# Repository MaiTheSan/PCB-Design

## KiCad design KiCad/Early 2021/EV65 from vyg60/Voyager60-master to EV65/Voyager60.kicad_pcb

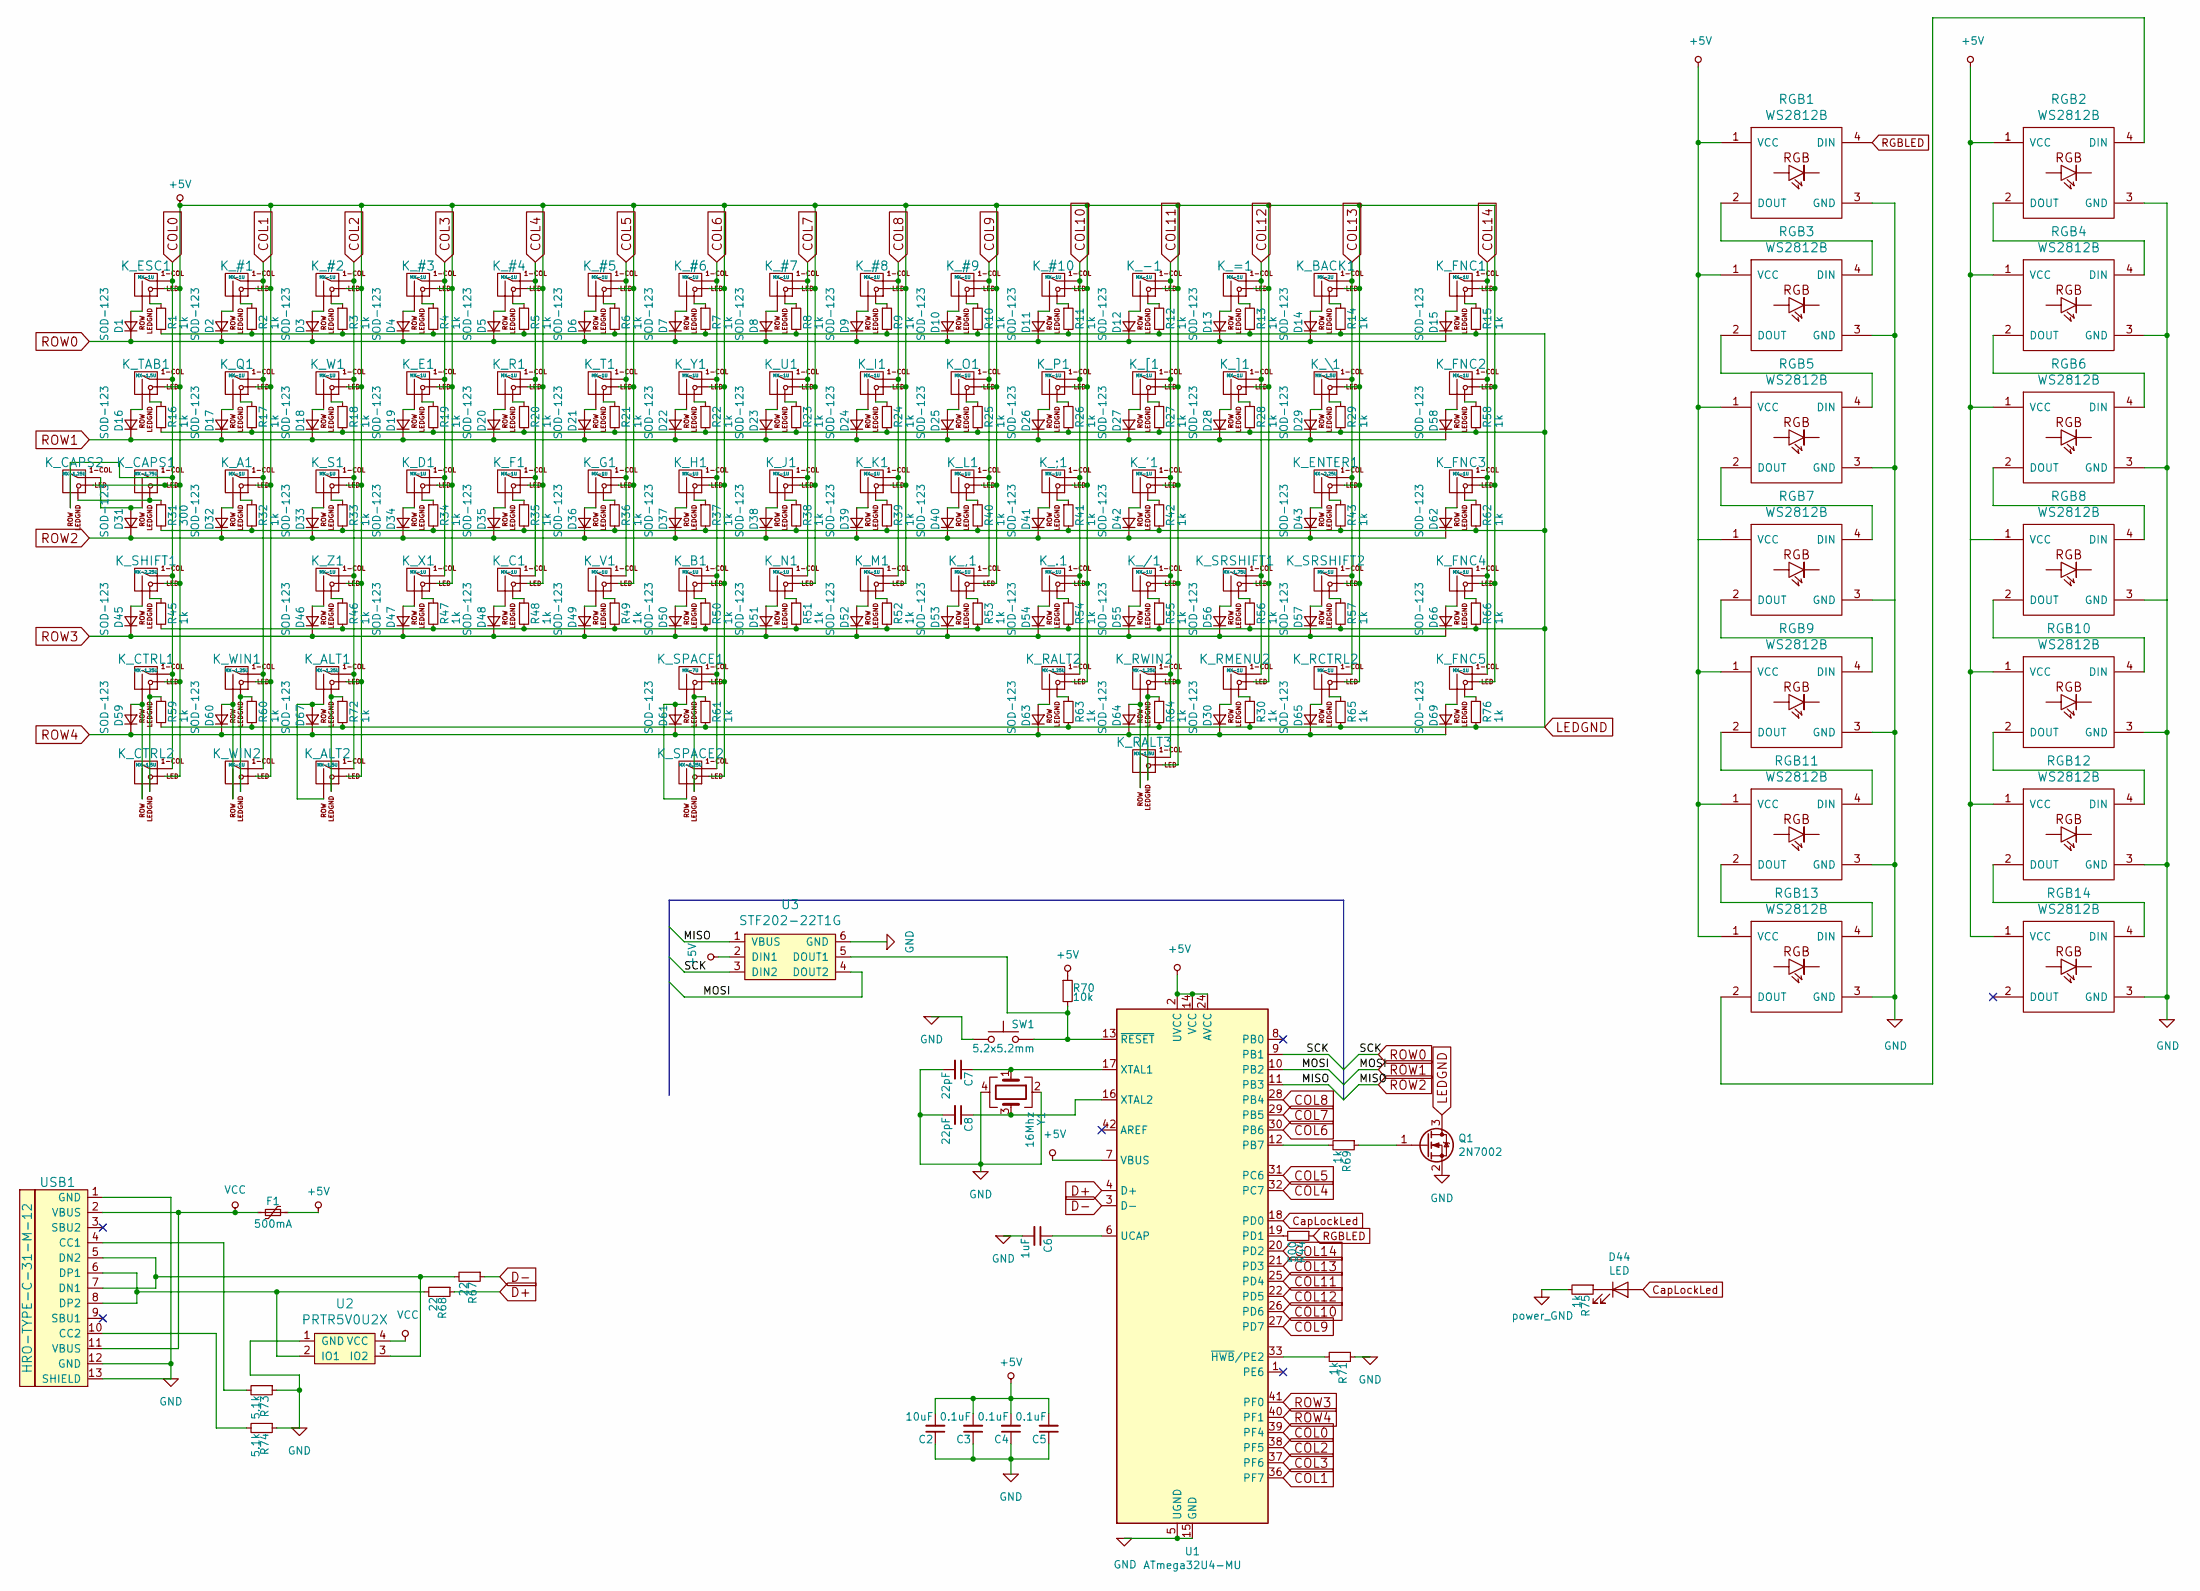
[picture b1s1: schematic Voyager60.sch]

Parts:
C2: 10uF; C_0603
C3, C4, C5: 0.1uF; C_0603
C6: 1uF; C_0603
C7, C8: 22pF; C_0603
D1, D2, D3, D4, D5, D6, D7, D8, D9, D10, D11, D12, D13, D14, D15, D16, D17, D18, D19, D20, D21, D22, D23, D24, D25, D26, D27, D28, D29, D30, D31, D32, D33, D34, D35, D36, D37, D38, D39, D40, D41, D42, D43, D45, D46, D47, D48, D49, D50, D51, D52, D53, D54, D55, D56, D57, D58, D59, D60, D61, D62, D63, D64, D65, D66, D67, D69: SOD-123; D_SOD-123
D44: LED; LED_D3.0mm
F1: 500mA; Fuse_SMD1206_Reflow
K_#1, K_#2, K_#3, K_#4, K_#5, K_#6, K_#7, K_#8, K_#9, K_#10: MX-1U; MXOnly-1U
K_'1: MX-1U; MXOnly-1U
K_,1: MX-1U; MXOnly-1U
K_-1: MX-1U; MXOnly-1U
K_.1: MX-1U; MXOnly-1U
K_/1: MX-1U; MXOnly-1U
K_;1: MX-1U; MXOnly-1U
K_=1: MX-1U; MXOnly-1U
K_A1: MX-1U; MXOnly-1U
K_ALT1: MX-1.25U; MXOnly-1.25U
K_ALT2: MX-1.5U; MXOnly-1.5U-FLIPPED
K_B1: MX-1U; MXOnly-1U
K_BACK1: MX-2U; MXOnly-2U
K_C1: MX-1U; MXOnly-1U
K_CAPS1: MX-1.75U; MXOnly-1.75U
K_CAPS2: MX-1.25U; MXOnly-1.25U-FLIPPED
K_CTRL1: MX-1.25U; MXOnly-1.25U
K_CTRL2: MX-1.5U; MXOnly-1.5U-FLIPPED
K_D1: MX-1U; MXOnly-1U
K_E1: MX-1U; MXOnly-1U
K_ENTER1: MX-2.25U; MXOnly-2.25U
K_ESC1: MX-1U; MXOnly-1U
K_F1: MX-1U; MXOnly-1U
K_FNC1, K_FNC2, K_FNC3, K_FNC4, K_FNC5: MX-1U; MXOnly-1U-FLIPPED
K_G1: MX-1U; MXOnly-1U
K_H1: MX-1U; MXOnly-1U
K_I1: MX-1U; MXOnly-1U
K_J1: MX-1U; MXOnly-1U
K_K1: MX-1U; MXOnly-1U
K_L1: MX-1U; MXOnly-1U
K_M1: MX-1U; MXOnly-1U
K_N1: MX-1U; MXOnly-1U
K_O1: MX-1U; MXOnly-1U
K_P1: MX-1U; MXOnly-1U
K_Q1: MX-1U; MXOnly-1U
K_R1: MX-1U; MXOnly-1U
K_RALT2: MX-1.25U; MXOnly-1.25U-FLIPPED
K_RALT3: MX-1.5U; MXOnly-1.5U-FLIPPED
K_RCTRL2: MX-1U; MXOnly-1U
K_RMENU2: MX-1U; MXOnly-1U
K_RWIN2: MX-1.25U; MXOnly-1.25U
K_S1: MX-1U; MXOnly-1U
K_SHIFT1: MX-2.25U; MXOnly-2.25U
K_SPACE1: MX-7U; MXOnly-7U-ReversedStabilizers
K_SPACE2: MX-6.25U; MXOnly-6.25U-ReversedStabilizers
K_SRSHIFT1: MX-1.75U; MXOnly-1.75U
K_SRSHIFT2: MX-1U; MXOnly-1U
K_T1: MX-1U; MXOnly-1U
K_TAB1: MX-1.5U; MXOnly-1.5U
K_U1: MX-1U; MXOnly-1U
K_V1: MX-1U; MXOnly-1U
K_W1: MX-1U; MXOnly-1U
K_WIN1: MX-1.25U; MXOnly-1.25U
K_WIN2: MX-1U; MXOnly-1U-FLIPPED
K_X1: MX-1U; MXOnly-1U
K_Y1: MX-1U; MXOnly-1U
K_Z1: MX-1U; MXOnly-1U
K_[1: MX-1U; MXOnly-1U
K_\1: MX-1.5U; MXOnly-1.5U
K_]1: MX-1U; MXOnly-1U
Q1: 2N7002; SOT-23
R1, R2, R3, R4, R5, R6, R7, R8, R9, R10, R11, R12, R13, R14, R15, R16, R17, R18, R19, R20, R21, R22, R23, R24, R25, R26, R27, R28, R29, R30, R32, R33, R34, R35, R36, R37, R38, R39, R40, R41, R42, R43, R45, R46, R47, R48, R49, R50, R51, R52, R53, R54, R55, R56, R57, R58, R59, R60, R61, R62, R63, R64, R65, R66, R69, R71, R72, R75, R76: 1k; R_0805
R31: 300; R_0805
R44: 500; R_0805
R67, R68: 22; R_0805
R70: 10k; R_0805
R73, R74: 5.1k; R_0805
RGB1, RGB2, RGB3, RGB4, RGB5, RGB6, RGB7, RGB8, RGB9, RGB10, RGB11, RGB12, RGB13, RGB14: WS2812B
SW1: 5.2x5.2mm; SKQG-1155865
U1: ATmega32U4-MU; QFN-44-1EP_7x7mm_Pitch0.5mm
U2: PRTR5V0U2X; SOT143B
U3: STF202-22T1G; Reset_Pretty
USB1: HRO-TYPE-C-31-M-12; HRO-TYPE-C-31-M-12-Assembly
Y1: 16Mhz; Crystal_SMD_3225-4Pin_3.2x2.5mm

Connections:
+5V: C2.2, C3.2, C4.2, C5.2, F1.1, K_#1.3 (LED), K_#2.3 (LED), K_#3.3 (LED), K_#4.3 (LED), K_#5.3 (LED), K_#6.3 (LED), K_#7.3 (LED), K_#8.3 (LED), K_#9.3 (LED), K_#10.3 (LED), K_'1.3 (LED), K_,1.3 (LED), K_-1.3 (LED), K_.1.3 (LED), K_/1.3 (LED), K_;1.3 (LED), K_=1.3 (LED), K_A1.3 (LED), K_ALT1.3 (LED), K_ALT2.3 (LED), K_B1.3 (LED), K_BACK1.3 (LED), K_C1.3 (LED), K_CAPS1.3 (LED), K_CAPS2.3 (LED), K_CTRL1.3 (LED), K_CTRL2.3 (LED), K_D1.3 (LED), K_E1.3 (LED), K_ENTER1.3 (LED), K_ESC1.3 (LED), K_F1.3 (LED), K_FNC1.3 (LED), K_FNC2.3 (LED), K_FNC3.3 (LED), K_FNC4.3 (LED), K_FNC5.3 (LED), K_G1.3 (LED), K_H1.3 (LED), K_I1.3 (LED), K_J1.3 (LED), K_K1.3 (LED), K_L1.3 (LED), K_M1.3 (LED), K_N1.3 (LED), K_O1.3 (LED), K_P1.3 (LED), K_Q1.3 (LED), K_R1.3 (LED), K_RALT2.3 (LED), K_RALT3.3 (LED), K_RCTRL2.3 (LED), K_RMENU2.3 (LED), K_RWIN2.3 (LED), K_S1.3 (LED), K_SHIFT1.3 (LED), K_SPACE1.3 (LED), K_SPACE2.3 (LED), K_SRSHIFT1.3 (LED), K_SRSHIFT2.3 (LED), K_T1.3 (LED), K_TAB1.3 (LED), K_U1.3 (LED), K_V1.3 (LED), K_W1.3 (LED), K_WIN1.3 (LED), K_WIN2.3 (LED), K_X1.3 (LED), K_Y1.3 (LED), K_Z1.3 (LED), K_[1.3 (LED), K_\1.3 (LED), K_]1.3 (LED), R70.1, RGB1.1 (VCC), RGB2.1 (VCC), RGB3.1 (VCC), RGB4.1 (VCC), RGB5.1 (VCC), RGB6.1 (VCC), RGB7.1 (VCC), RGB8.1 (VCC), RGB9.1 (VCC), RGB10.1 (VCC), RGB11.1 (VCC), RGB12.1 (VCC), RGB13.1 (VCC), RGB14.1 (VCC), U1.2 (UVCC), U1.7 (VBUS), U1.14 (VCC), U1.24 (AVCC), U1.34 (VCC), U1.44 (AVCC), U3.2 (DIN1)
COL0: K_CAPS1.1 (COL), K_CAPS2.2 (ROW), K_CTRL1.1 (COL), K_CTRL2.1 (COL), K_ESC1.1 (COL), K_SHIFT1.1 (COL), K_TAB1.1 (COL), U1.39 (PF4)
COL1: K_#1.1 (COL), K_A1.1 (COL), K_Q1.1 (COL), K_WIN1.1 (COL), K_WIN2.1 (COL), U1.36 (PF7)
COL2: K_#2.1 (COL), K_ALT1.1 (COL), K_ALT2.1 (COL), K_S1.1 (COL), K_W1.1 (COL), K_Z1.1 (COL), U1.38 (PF5)
COL3: K_#3.1 (COL), K_D1.1 (COL), K_E1.1 (COL), K_X1.1 (COL), U1.37 (PF6)
COL4: K_#4.1 (COL), K_C1.1 (COL), K_F1.1 (COL), K_R1.1 (COL), U1.32 (PC7)
COL5: K_#5.1 (COL), K_G1.1 (COL), K_T1.1 (COL), K_V1.1 (COL), U1.31 (PC6)
COL6: K_#6.1 (COL), K_B1.1 (COL), K_H1.1 (COL), K_SPACE1.1 (COL), K_SPACE2.1 (COL), K_Y1.1 (COL), U1.30 (PB6)
COL7: K_#7.1 (COL), K_J1.1 (COL), K_N1.1 (COL), K_U1.1 (COL), U1.29 (PB5)
COL8: K_#8.1 (COL), K_I1.1 (COL), K_K1.1 (COL), K_M1.1 (COL), U1.28 (PB4)
COL9: K_#9.1 (COL), K_,1.1 (COL), K_L1.1 (COL), K_O1.1 (COL), U1.27 (PD7)
COL10: K_#10.1 (COL), K_.1.1 (COL), K_;1.1 (COL), K_P1.1 (COL), K_RALT2.1 (COL), U1.26 (PD6)
COL11: K_'1.1 (COL), K_-1.1 (COL), K_/1.1 (COL), K_RALT3.1 (COL), K_RWIN2.1 (COL), K_[1.1 (COL), U1.25 (PD4)
COL12: K_=1.1 (COL), K_RMENU2.1 (COL), K_SRSHIFT1.1 (COL), K_]1.1 (COL), U1.22 (PD5)
COL13: K_BACK1.1 (COL), K_ENTER1.1 (COL), K_RCTRL2.1 (COL), K_SRSHIFT2.1 (COL), K_\1.1 (COL), U1.21 (PD3)
COL14: K_FNC1.1 (COL), K_FNC2.1 (COL), K_FNC3.1 (COL), K_FNC4.1 (COL), K_FNC5.1 (COL), U1.20 (PD2)
CapLockLed: D44.2 (A), U1.18 (PD0)
D+: R68.1, U1.4 (D+)
D-: R67.1, U1.3 (D-)
LEDGND: Q1.3 (D), R1.2, R2.2, R3.2, R4.2, R5.2, R6.2, R7.2, R8.2, R9.2, R10.2, R11.2, R12.2, R13.2, R14.2, R15.2, R16.2, R17.2, R18.2, R19.2, R20.2, R21.2, R22.2, R23.2, R24.2, R25.2, R26.2, R27.2, R28.2, R29.2, R30.2, R31.2, R32.2, R33.2, R34.2, R35.2, R36.2, R37.2, R38.2, R39.2, R40.2, R41.2, R42.2, R43.2, R45.2, R46.2, R47.2, R48.2, R49.2, R50.2, R51.2, R52.2, R53.2, R54.2, R55.2, R56.2, R57.2, R58.2, R59.2, R60.2, R61.2, R62.2, R63.2, R64.2, R65.2, R66.2, R72.2, R76.2
unnamed: C6.1, U1.6 (UCAP)
unnamed: C7.1, U1.17 (XTAL1), Y1.1
unnamed: C8.1, U1.16 (XTAL2), Y1.3
unnamed: D1.2 (A), K_ESC1.2 (ROW)
unnamed: D2.2 (A), K_#1.2 (ROW)
unnamed: D3.2 (A), K_#2.2 (ROW)
unnamed: D4.2 (A), K_#3.2 (ROW)
unnamed: D5.2 (A), K_#4.2 (ROW)
unnamed: D6.2 (A), K_#5.2 (ROW)
unnamed: D7.2 (A), K_#6.2 (ROW)
unnamed: D8.2 (A), K_#7.2 (ROW)
unnamed: D9.2 (A), K_#8.2 (ROW)
unnamed: D10.2 (A), K_#9.2 (ROW)
unnamed: D11.2 (A), K_#10.2 (ROW)
unnamed: D12.2 (A), K_-1.2 (ROW)
unnamed: D13.2 (A), K_=1.2 (ROW)
unnamed: D14.2 (A), K_BACK1.2 (ROW)
unnamed: D15.2 (A), K_FNC1.2 (ROW)
unnamed: D16.2 (A), K_TAB1.2 (ROW)
unnamed: D17.2 (A), K_Q1.2 (ROW)
unnamed: D18.2 (A), K_W1.2 (ROW)
unnamed: D19.2 (A), K_E1.2 (ROW)
unnamed: D20.2 (A), K_R1.2 (ROW)
unnamed: D21.2 (A), K_T1.2 (ROW)
unnamed: D22.2 (A), K_Y1.2 (ROW)
unnamed: D23.2 (A), K_U1.2 (ROW)
unnamed: D24.2 (A), K_I1.2 (ROW)
unnamed: D25.2 (A), K_O1.2 (ROW)
unnamed: D26.2 (A), K_P1.2 (ROW)
unnamed: D27.2 (A), K_[1.2 (ROW)
unnamed: D28.2 (A), K_]1.2 (ROW)
unnamed: D29.2 (A), K_\1.2 (ROW)
unnamed: D30.2 (A), K_RMENU2.2 (ROW)
unnamed: D31.2 (A), K_CAPS1.2 (ROW), K_CAPS2.1 (COL)
unnamed: D32.2 (A), K_A1.2 (ROW)
unnamed: D33.2 (A), K_S1.2 (ROW)
unnamed: D34.2 (A), K_D1.2 (ROW)
unnamed: D35.2 (A), K_F1.2 (ROW)
unnamed: D36.2 (A), K_G1.2 (ROW)
unnamed: D37.2 (A), K_H1.2 (ROW)
unnamed: D38.2 (A), K_J1.2 (ROW)
unnamed: D39.2 (A), K_K1.2 (ROW)
unnamed: D40.2 (A), K_L1.2 (ROW)
unnamed: D41.2 (A), K_;1.2 (ROW)
unnamed: D42.2 (A), K_'1.2 (ROW)
unnamed: D43.2 (A), K_ENTER1.2 (ROW)
unnamed: D44.1 (K), R75.1
unnamed: D45.2 (A), K_SHIFT1.2 (ROW)
unnamed: D46.2 (A), K_Z1.2 (ROW)
unnamed: D47.2 (A), K_X1.2 (ROW)
unnamed: D48.2 (A), K_C1.2 (ROW)
unnamed: D49.2 (A), K_V1.2 (ROW)
unnamed: D50.2 (A), K_B1.2 (ROW)
unnamed: D51.2 (A), K_N1.2 (ROW)
unnamed: D52.2 (A), K_M1.2 (ROW)
unnamed: D53.2 (A), K_,1.2 (ROW)
unnamed: D54.2 (A), K_.1.2 (ROW)
unnamed: D55.2 (A), K_/1.2 (ROW)
unnamed: D56.2 (A), K_SRSHIFT1.2 (ROW)
unnamed: D57.2 (A), K_SRSHIFT2.2 (ROW)
unnamed: D58.2 (A), K_FNC2.2 (ROW)
unnamed: D59.2 (A), K_CTRL1.2 (ROW), K_CTRL2.2 (ROW)
unnamed: D60.2 (A), K_WIN1.2 (ROW), K_WIN2.2 (ROW)
unnamed: D61.2 (A), K_SPACE1.2 (ROW), K_SPACE2.2 (ROW)
unnamed: D62.2 (A), K_FNC3.2 (ROW)
unnamed: D63.2 (A), K_RALT2.2 (ROW)
unnamed: D64.2 (A), K_RALT3.2 (ROW), K_RWIN2.2 (ROW)
unnamed: D65.2 (A), K_RCTRL2.2 (ROW)
unnamed: D66.2 (A), K_FNC4.2 (ROW)
unnamed: D67.2 (A), K_ALT1.2 (ROW), K_ALT2.2 (ROW)
unnamed: D69.2 (A), K_FNC5.2 (ROW)
unnamed: K_#1.4 (LEDGND), R2.1
unnamed: K_#2.4 (LEDGND), R3.1
unnamed: K_#3.4 (LEDGND), R4.1
unnamed: K_#4.4 (LEDGND), R5.1
unnamed: K_#5.4 (LEDGND), R6.1
unnamed: K_#6.4 (LEDGND), R7.1
unnamed: K_#7.4 (LEDGND), R8.1
unnamed: K_#8.4 (LEDGND), R9.1
unnamed: K_#9.4 (LEDGND), R10.1
unnamed: K_#10.4 (LEDGND), R11.1
unnamed: K_'1.4 (LEDGND), R42.1
unnamed: K_,1.4 (LEDGND), R53.1
unnamed: K_-1.4 (LEDGND), R12.1
unnamed: K_.1.4 (LEDGND), R54.1
unnamed: K_/1.4 (LEDGND), R55.1
unnamed: K_;1.4 (LEDGND), R41.1
unnamed: K_=1.4 (LEDGND), R13.1
unnamed: K_A1.4 (LEDGND), R32.1
unnamed: K_ALT1.4 (LEDGND), K_ALT2.4 (LEDGND), R72.1
unnamed: K_B1.4 (LEDGND), R50.1
unnamed: K_BACK1.4 (LEDGND), R14.1
unnamed: K_C1.4 (LEDGND), R48.1
unnamed: K_CAPS1.4 (LEDGND), K_CAPS2.4 (LEDGND), R31.1
unnamed: K_CTRL1.4 (LEDGND), K_CTRL2.4 (LEDGND), R59.1
unnamed: K_D1.4 (LEDGND), R34.1
unnamed: K_E1.4 (LEDGND), R19.1
unnamed: K_ENTER1.4 (LEDGND), R43.1
unnamed: K_ESC1.4 (LEDGND), R1.1
unnamed: K_F1.4 (LEDGND), R35.1
unnamed: K_FNC1.4 (LEDGND), R15.1
unnamed: K_FNC2.4 (LEDGND), R58.1
unnamed: K_FNC3.4 (LEDGND), R62.1
unnamed: K_FNC4.4 (LEDGND), R66.1
unnamed: K_FNC5.4 (LEDGND), R76.1
unnamed: K_G1.4 (LEDGND), R36.1
unnamed: K_H1.4 (LEDGND), R37.1
unnamed: K_I1.4 (LEDGND), R24.1
unnamed: K_J1.4 (LEDGND), R38.1
unnamed: K_K1.4 (LEDGND), R39.1
unnamed: K_L1.4 (LEDGND), R40.1
unnamed: K_M1.4 (LEDGND), R52.1
unnamed: K_N1.4 (LEDGND), R51.1
unnamed: K_O1.4 (LEDGND), R25.1
unnamed: K_P1.4 (LEDGND), R26.1
unnamed: K_Q1.4 (LEDGND), R17.1
unnamed: K_R1.4 (LEDGND), R20.1
unnamed: K_RALT2.4 (LEDGND), R63.1
unnamed: K_RALT3.4 (LEDGND), K_RWIN2.4 (LEDGND), R64.1
unnamed: K_RCTRL2.4 (LEDGND), R65.1
unnamed: K_RMENU2.4 (LEDGND), R30.1
unnamed: K_S1.4 (LEDGND), R33.1
unnamed: K_SHIFT1.4 (LEDGND), R45.1
unnamed: K_SPACE1.4 (LEDGND), K_SPACE2.4 (LEDGND), R61.1
unnamed: K_SRSHIFT1.4 (LEDGND), R56.1
unnamed: K_SRSHIFT2.4 (LEDGND), R57.1
unnamed: K_T1.4 (LEDGND), R21.1
unnamed: K_TAB1.4 (LEDGND), R16.1
unnamed: K_U1.4 (LEDGND), R23.1
unnamed: K_V1.4 (LEDGND), R49.1
unnamed: K_W1.4 (LEDGND), R18.1
unnamed: K_WIN1.4 (LEDGND), K_WIN2.4 (LEDGND), R60.1
unnamed: K_X1.4 (LEDGND), R47.1
unnamed: K_Y1.4 (LEDGND), R22.1
unnamed: K_Z1.4 (LEDGND), R46.1
unnamed: K_[1.4 (LEDGND), R27.1
unnamed: K_\1.4 (LEDGND), R29.1
unnamed: K_]1.4 (LEDGND), R28.1
unnamed: Q1.1 (G), R69.1
unnamed: R44.2, U1.19 (PD1)
unnamed: R67.2, U2.3 (IO2), USB1.5 (DN2), USB1.7 (DN1)
unnamed: R68.2, U2.2 (IO1), USB1.6 (DP1), USB1.8 (DP2)
unnamed: R69.2, U1.12 (PB7)
unnamed: R70.2, SW1.2, U1.13 (~RESET), U3.5 (DOUT1)
unnamed: R71.2, U1.33 (~HWB~/PE2)
unnamed: R73.2, USB1.4 (CC1)
unnamed: R74.2, USB1.10 (CC2)
unnamed: RGB1.2 (DOUT), RGB3.4 (DIN)
unnamed: RGB2.2 (DOUT), RGB4.4 (DIN)
unnamed: RGB3.2 (DOUT), RGB5.4 (DIN)
unnamed: RGB4.2 (DOUT), RGB6.4 (DIN)
unnamed: RGB5.2 (DOUT), RGB7.4 (DIN)
unnamed: RGB6.2 (DOUT), RGB8.4 (DIN)
unnamed: RGB7.2 (DOUT), RGB9.4 (DIN)
unnamed: RGB10.2 (DOUT), RGB12.4 (DIN)
unnamed: RGB8.2 (DOUT), RGB10.4 (DIN)
unnamed: RGB11.2 (DOUT), RGB13.4 (DIN)
unnamed: RGB9.2 (DOUT), RGB11.4 (DIN)
unnamed: RGB12.2 (DOUT), RGB14.4 (DIN)
unnamed: RGB2.4 (DIN), RGB13.2 (DOUT)
RGBLED: R44.1, RGB1.4 (DIN)
ROW0: D1.1 (K), D2.1 (K), D3.1 (K), D4.1 (K), D5.1 (K), D6.1 (K), D7.1 (K), D8.1 (K), D9.1 (K), D10.1 (K), D11.1 (K), D12.1 (K), D13.1 (K), D14.1 (K), D15.1 (K), U1.9 (PB1), U3.3 (DIN2)
ROW1: D16.1 (K), D17.1 (K), D18.1 (K), D19.1 (K), D20.1 (K), D21.1 (K), D22.1 (K), D23.1 (K), D24.1 (K), D25.1 (K), D26.1 (K), D27.1 (K), D28.1 (K), D29.1 (K), D58.1 (K), U1.10 (PB2), U3.4 (DOUT2)
ROW2: D31.1 (K), D32.1 (K), D33.1 (K), D34.1 (K), D35.1 (K), D36.1 (K), D37.1 (K), D38.1 (K), D39.1 (K), D40.1 (K), D41.1 (K), D42.1 (K), D43.1 (K), D62.1 (K), U1.11 (PB3), U3.1 (VBUS)
ROW3: D45.1 (K), D46.1 (K), D47.1 (K), D48.1 (K), D49.1 (K), D50.1 (K), D51.1 (K), D52.1 (K), D53.1 (K), D54.1 (K), D55.1 (K), D56.1 (K), D57.1 (K), D66.1 (K), U1.41 (PF0)
ROW4: D30.1 (K), D59.1 (K), D60.1 (K), D61.1 (K), D63.1 (K), D64.1 (K), D65.1 (K), D67.1 (K), D69.1 (K), U1.40 (PF1)
VCC: F1.2, U2.4 (VCC), USB1.2 (VBUS), USB1.11 (VBUS)

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
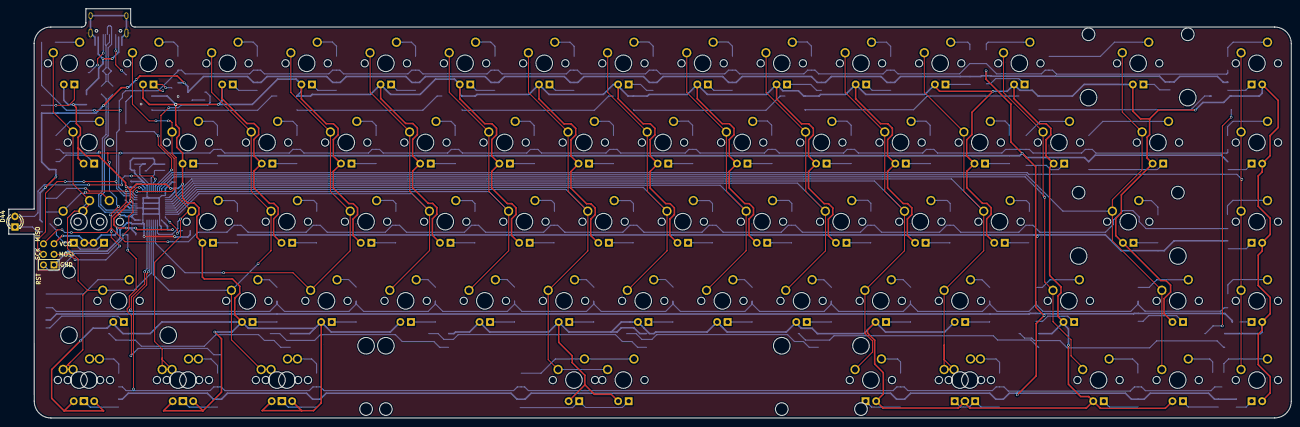
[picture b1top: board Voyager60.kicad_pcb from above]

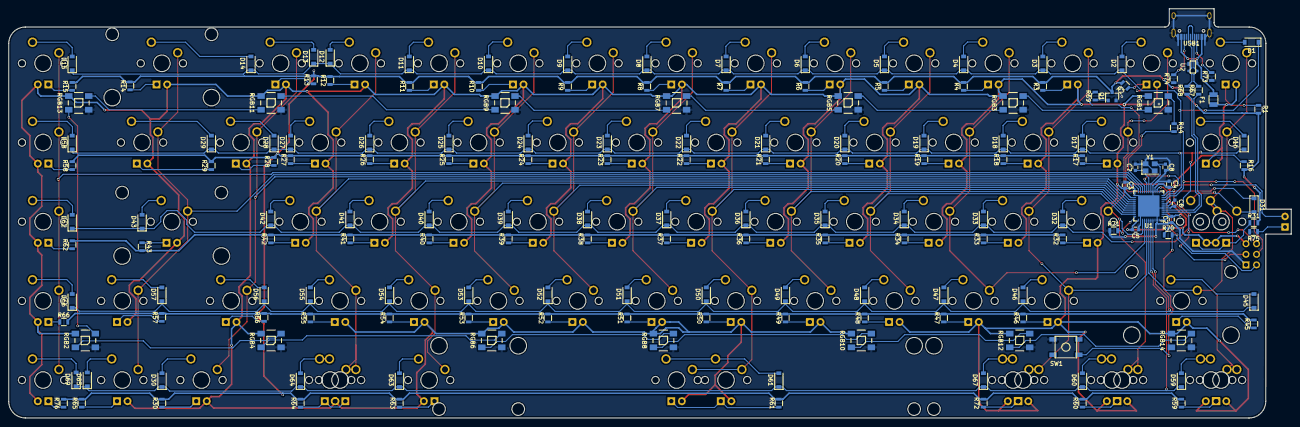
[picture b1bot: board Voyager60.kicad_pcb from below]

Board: 2 copper layers, 308.5 x 98.4 mm, 246 parts (171 on the bottom side), 188 nets.

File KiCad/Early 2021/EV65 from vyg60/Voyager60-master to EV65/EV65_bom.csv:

Component,Description,Part,References,Value,Footprint,Quantity Per PCB,Datasheet
1,"Capacitor, Ceramic, 15V or more",C_Small,C3 C4 C5,0.1uF,C_0603,3,
2,"Capacitor, Ceramic, 15V or more",C_Small,C2,10uF,C_0603,1,
3,"Capacitor, Ceramic, 15V or more",C_Small,C6,1uF,C_0603,1,
4,"Capacitor, Ceramic, 15V or more",C_Small,C7 C8,22pF,C_0603,2,
5,"Diode, Generic",D_Small,D1 D2 D3 D4 D5 D6 D7 D8 D9 D10 D11 D12 D13 D14 D16 D17 D18 D19 D20 D21 D22 D23 D24 D25 D26 D27 D28 D29 D30 D31 D32 D33 D34 D35 D36 D37 D38 D39 D40 D41 D42 D43 D45 D46 D47 D48 D49 D50 D51 D52 D53 D54 D55 D56 D57 D58 D59 D60 D61 D62 D63 D64 D65 D67 D69,SOD-123,D_SOD-123,66,
6,"Polyfuse, 500mA hold, 1A trip",Polyfuse_Small,F1,500mA,Fuse_SMD1206_Reflow,1,
7,N-Channel MOSFET,2N7002,Q1,2N7002,SOT-23,1,https://www.fairchildsemi.com/datasheets/2N/2N7002.pdf
8,"Resistor, Generic",R_Small,R70,10k,R_0805,1,
9,"resistor, Generic",R_Small,R31,300,R_0805,1,
10,"Resistor, Generic",R_Small,R1 R2 R3 R4 R5 R6 R7 R8 R9 R10 R11 R12 R13 R14 R16 R17 R18 R19 R20 R21 R22 R23 R24 R25 R26 R27 R28 R29 R30 R32 R33 R34 R35 R36 R37 R38 R39 R40 R41 R42 R43 R45 R46 R47 R48 R49 R50 R51 R52 R53 R54 R55 R56 R57 R58 R59 R60 R61 R62 R63 R64 R65 R66 R69 R71 R72 R76,1k,R_0805,69,
11,"Resistor, Generic",R_Small,R67 R68,22,R_0805,2,
12,"Resistor, Generic",R_Small,R73 R74,5.1k,R_0805,2,
13,"Resistor, Generic",R_Small,R44,500,R_0805,1,
14,"WS2812B RGB LED, 5050",WS2812B,RGB1 RGB2 RGB3 RGB4 RGB5 RGB6 RGB7 RGB8 RGB9 RGB10 RGB11 RGB12 RGB13 RGB14,WS2812B,WS2812B,14,
15,"5.2 x 5.2mm Push Button, SMT",SW_Push,SW1,5.2x5.2mm,SKQG-1155865,1,
16,ATmega32U4-MU,ATmega32U4-MU-MCU_Microchip_ATmega,U1,ATmega32U4-MU,QFN-44-1EP_7x7mm_Pitch0.5mm,1,http://ww1.microchip.com/downloads/en/DeviceDoc/Atmel-7766-8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
17,ESD Protection IC,PRTR5V0U2X,U2,PRTR5V0U2X,SOT143B,1,
18,USB Type-C Connector,HRO-TYPE-C-31-M-12,USB1,HRO-TYPE-C-31-M-12,HRO-TYPE-C-31-M-12-Assembly,1,
,"Crystal, 3.2 x 2.5mm, 16MHz",Crystal_GND24,Y1,16Mhz,Crystal_SMD_3225-4pin_3.2x2.5mm,1,

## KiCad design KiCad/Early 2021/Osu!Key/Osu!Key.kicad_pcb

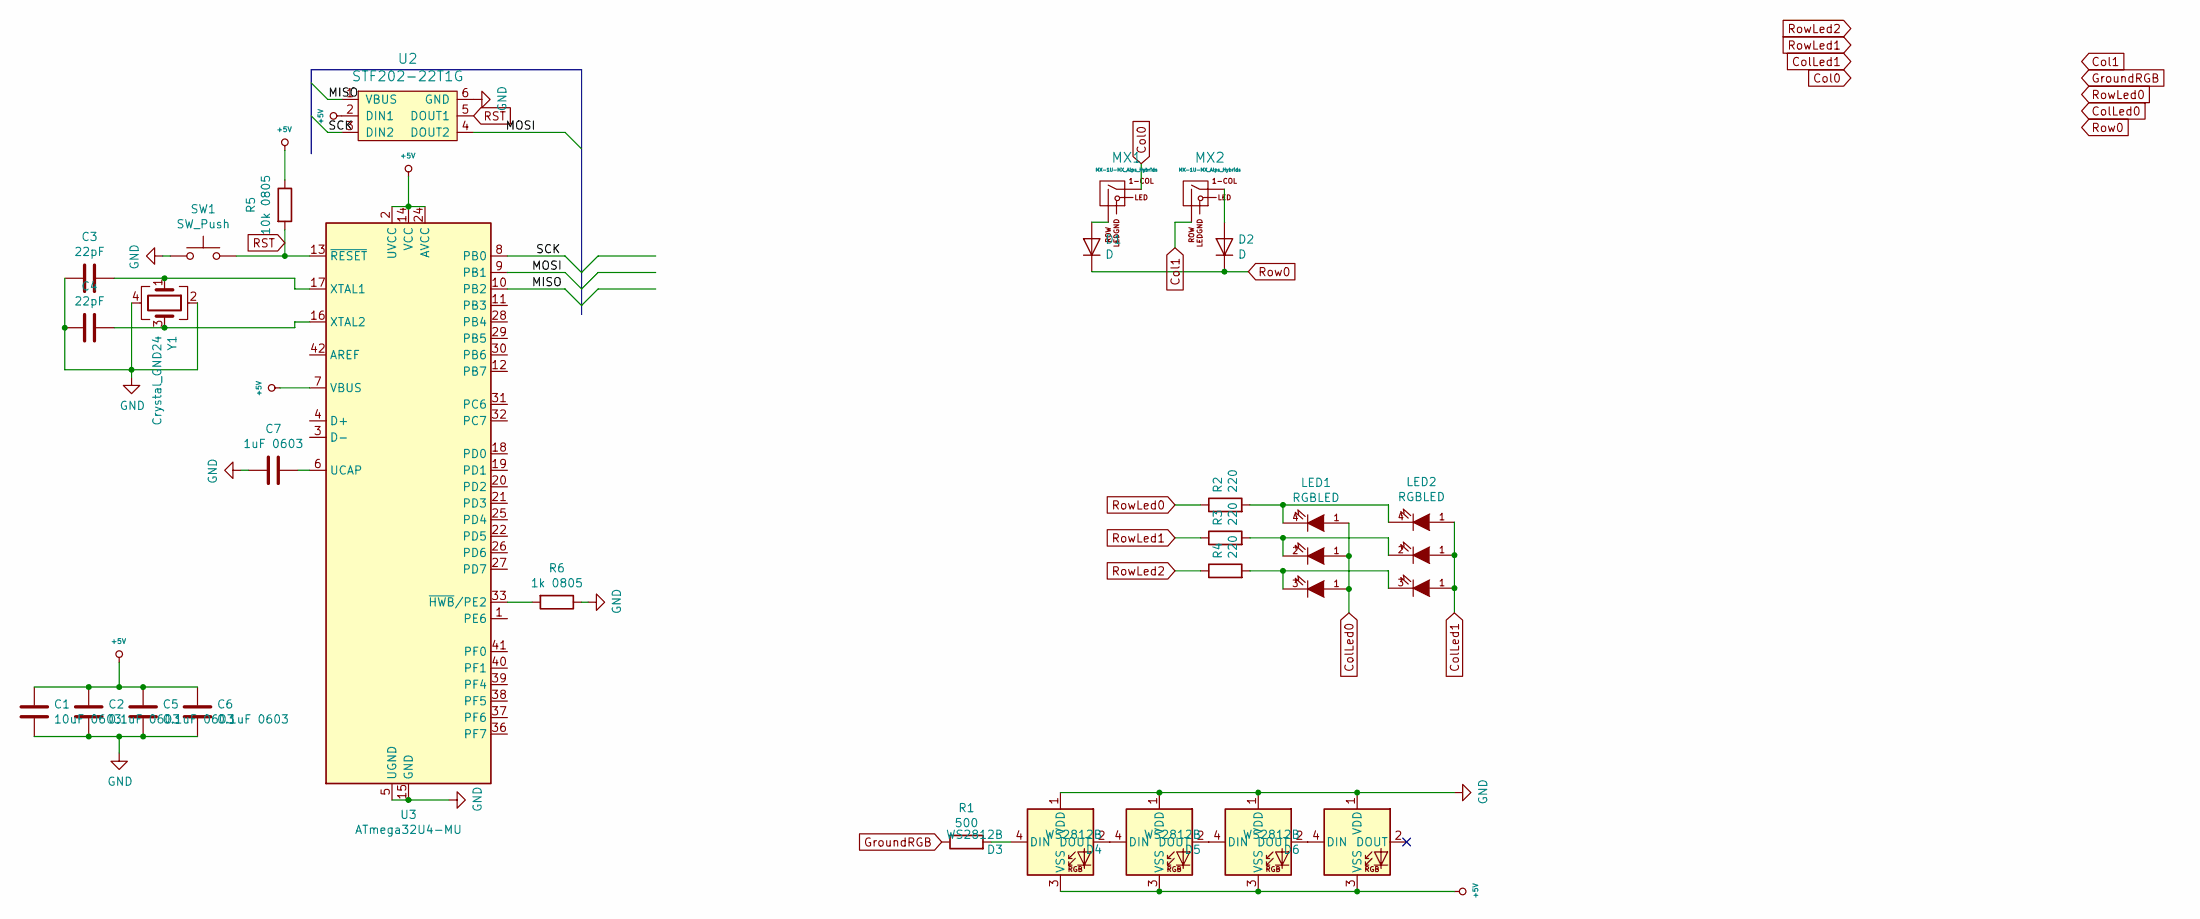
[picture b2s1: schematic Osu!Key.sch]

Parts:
C1: 10uF 0603; C_0603
C2, C5, C6: 0.1uF 0603; C_0603
C3, C4: 22pF; C_0603
C7: 1uF 0603; C_0603
D1, D2: D; D_SOD-123-Pretty
D3, D4, D5, D6: WS2812B; LED_WS2812B_PLCC4_5.0x5.0mm_P3.2mm
LED1, LED2: RGBLED; RGB-6028
MX1, MX2: MX-1U-MX_Alps_Hybrids; MXOnly-1U-Hotswap
R1: 500; R_0805
R2, R3, R4: 220; R_0805
R5: 10k 0805; R_0805
R6: 1k 0805; R_0805
SW1: SW_Push; SKQGADE010
U2: STF202-22T1G; Reset_Pretty
U3: ATmega32U4-MU; QFN-44-1EP_7x7mm_P0.5mm_EP5.2x5.2mm
Y1: Crystal_GND24; Crystal_SMD_3225-4Pin_3.2x2.5mm

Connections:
+5V: C1.1, C2.1, C5.1, C6.1, D3.3 (VSS), D4.3 (VSS), D5.3 (VSS), D6.3 (VSS), R5.1, U2.2 (DIN1), U3.2 (UVCC), U3.7 (VBUS), U3.14 (VCC), U3.24 (AVCC), U3.34 (VCC), U3.44 (AVCC)
/MISO: U2.1 (VBUS), U3.10 (PB2)
/MOSI: U2.4 (DOUT2), U3.9 (PB1)
/SCK: U2.3 (DIN2), U3.8 (PB0)
Col0: MX1.1 (COL)
ColLed0: LED1.1 (A)
ColLed1: LED2.1 (A)
GND: C1.2, C2.2, C3.2, C4.2, C5.2, C6.2, C7.2, D3.1 (VDD), D4.1 (VDD), D5.1 (VDD), D6.1 (VDD), R6.1, SW1.1, U2.6 (GND), U3.5 (UGND), U3.15 (GND), U3.23 (GND), U3.35 (GND), U3.43 (GND), U3.45 (GND), Y1.2, Y1.4
GroundRGB: R1.1
unnamed: C3.1, U3.17 (XTAL1), Y1.1
unnamed: C4.1, U3.16 (XTAL2), Y1.3
unnamed: C7.1, U3.6 (UCAP)
unnamed: D1.2 (A), MX1.2 (ROW)
unnamed: D3.2 (DOUT), D4.4 (DIN)
unnamed: D3.4 (DIN), R1.2
unnamed: D4.2 (DOUT), D5.4 (DIN)
unnamed: D5.2 (DOUT), D6.4 (DIN)
unnamed: LED1.2 (R), LED2.2 (R), R3.2
unnamed: LED1.3 (G), LED2.3 (G), R4.2
unnamed: LED1.4 (B), LED2.4 (B), R2.2
unnamed: R6.2, U3.33 (~HWB~/PE2)
RST: R5.2, SW1.2, U2.5 (DOUT1), U3.13 (~RESET)
Row0: D1.1 (K), D2.1 (K)
RowLed0: R2.1
RowLed1: R3.1
RowLed2: R4.1

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
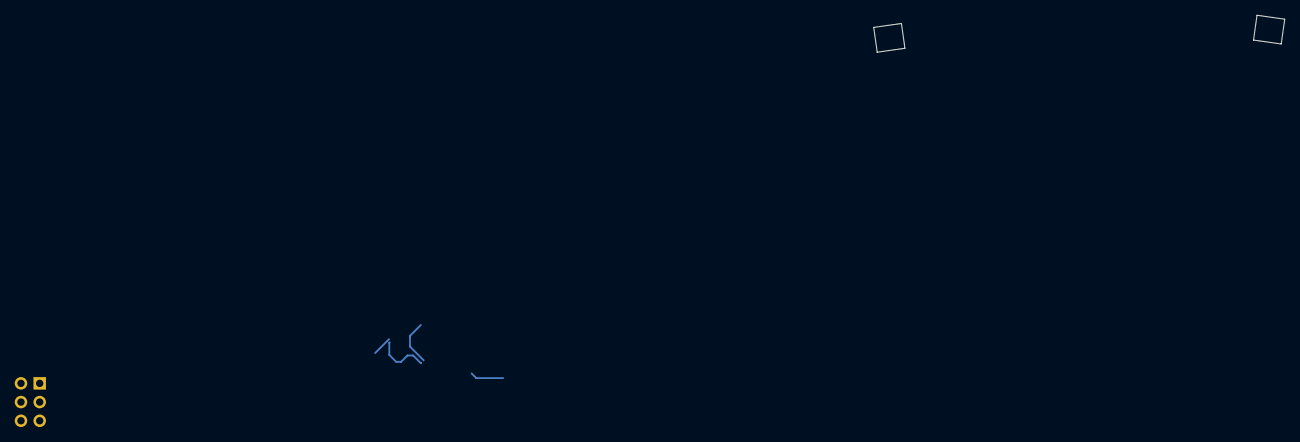
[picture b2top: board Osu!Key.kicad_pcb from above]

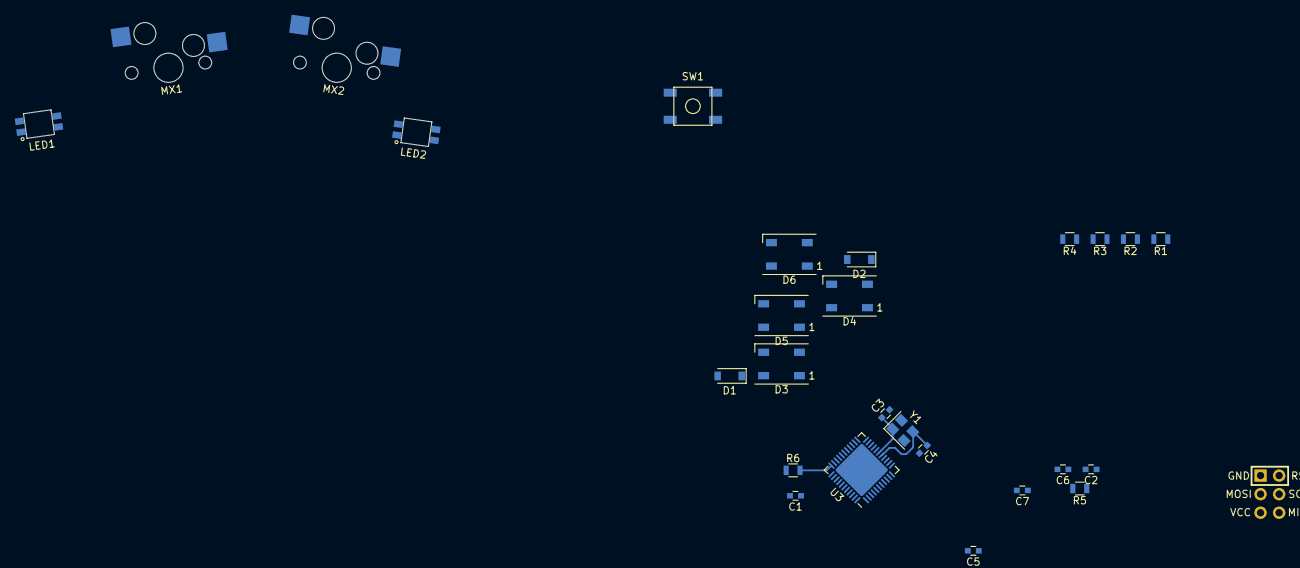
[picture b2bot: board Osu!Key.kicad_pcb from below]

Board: 2 copper layers, 27 parts (25 on the bottom side), 20 nets.
